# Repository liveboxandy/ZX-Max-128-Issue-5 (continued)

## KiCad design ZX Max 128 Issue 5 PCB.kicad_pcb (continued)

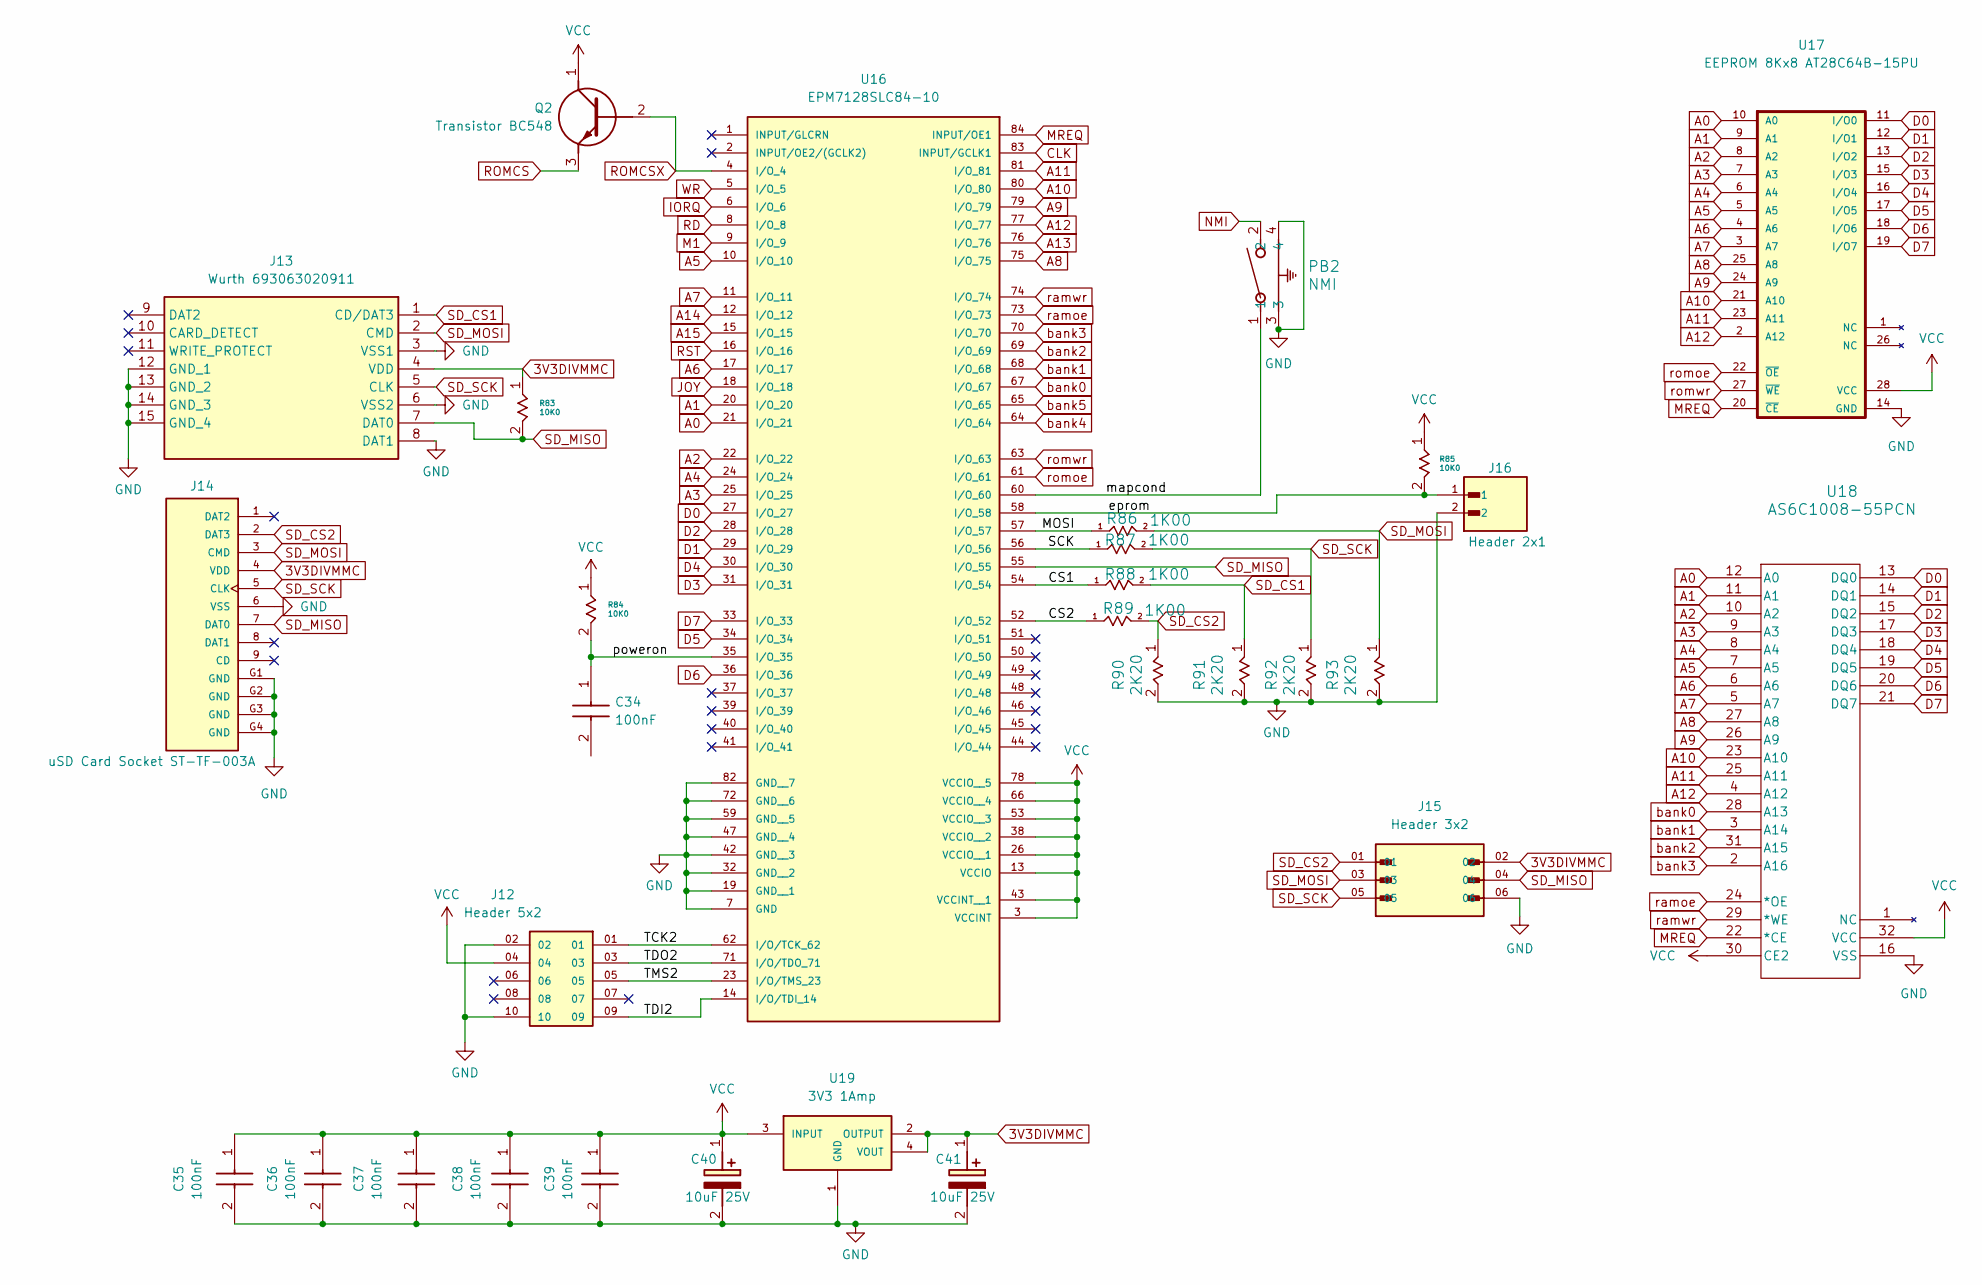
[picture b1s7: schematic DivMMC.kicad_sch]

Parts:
C34, C35, C36, C37, C38, C39: 100nF; CAPRB250W50L400T250H550; Mouser Part Number 594-K104Z15Y5VF5TL2
C40, C41: 10uF 25V; CAPPRD200W50D500H1100; Mouser Part Number 667-ECA-1EM100B
J12: Header 5x2; AMPHENOL_10129381-910002BLF; PARTREV D
J13: Wurth 693063020911; SD Card Connector Wurth 693063020911; Mouser Part Number 710-693063020911
J14: uSD Card Socket ST-TF-003A; SUNTECH_ST-TF-003A
J15: Header 3x2; AMPHENOL_10129381-906002BLF
J16: Header 2x1; HARWIN_M20-9990246; PARTREV 14
PB2: NMI; SW2_1825027-G_TEC
Q2: Transistor BC548; BC548BTA
R83, R84, R85: 10K0; STA_CF14_STP
R86, R87, R88, R89: 1K00; STA_CF14_STP
R90, R91, R92, R93: 2K20; STA_CF14_STP
U16: EPM7128SLC84-10; PLCC84AT
U17: EEPROM 8Kx8 AT28C64B-15PU; DIP1555W45P254L3733H482Q28
U18: AS6C1008-55PCN; PDIP-32_MIL600_ALL
U19: 3V3 1Amp; SOT230P700X185-4N

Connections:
3V3DIVMMC: C41.1 (+), J13.4 (VDD), J14.4 (VDD), J15.02, R83.1, U19.2 (OUTPUT), U19.4 (VOUT)
/DivMMC/CS1: R88.1, U16.54 (I/O_54)
/DivMMC/CS2: R89.1, U16.52 (I/O_52)
/DivMMC/MOSI: R86.1, U16.57 (I/O_57)
/DivMMC/SCK: R87.1, U16.56 (I/O_56)
/DivMMC/TCK2: J12.01, U16.62 (I/O/TCK_62)
/DivMMC/TDI2: J12.09, U16.14 (I/O/TDI_14)
/DivMMC/TDO2: J12.03, U16.71 (I/O/TDO_71)
/DivMMC/TMS2: J12.05, U16.23 (I/O/TMS_23)
/DivMMC/eprom: J16.1, R85.2, U16.58 (I/O_58)
/DivMMC/mapcond: PB2.1, U16.60 (I/O_60)
/DivMMC/poweron: C34.1 (+_1), R84.2, U16.35 (I/O_35)
A0: U16.21 (I/O_21), U17.10 (A0), U18.12 (A0); also elsewhere on the board
A1: U16.20 (I/O_20), U17.9 (A1), U18.11 (A1); also elsewhere on the board
A2: U16.22 (I/O_22), U17.8 (A2), U18.10 (A2); also elsewhere on the board
A3: U16.25 (I/O_25), U17.7 (A3), U18.9 (A3); also elsewhere on the board
A4: U16.24 (I/O_24), U17.6 (A4), U18.8 (A4); also elsewhere on the board
A5: U16.10 (I/O_10), U17.5 (A5), U18.7 (A5); also elsewhere on the board
A6: U16.17 (I/O_17), U17.4 (A6), U18.6 (A6); also elsewhere on the board
A7: U16.11 (I/O_11), U17.3 (A7), U18.5 (A7); also elsewhere on the board
A8: U16.75 (I/O_75), U17.25 (A8), U18.27 (A8); also elsewhere on the board
A9: U16.79 (I/O_79), U17.24 (A9), U18.26 (A9); also elsewhere on the board
A10: U16.80 (I/O_80), U17.21 (A10), U18.23 (A10); also elsewhere on the board
A11: U16.81 (I/O_81), U17.23 (A11), U18.25 (A11); also elsewhere on the board
A12: U16.77 (I/O_77), U17.2 (A12), U18.4 (A12); also elsewhere on the board
A13: U16.76 (I/O_76); also elsewhere on the board
A14: U16.12 (I/O_12); also elsewhere on the board
A15: U16.15 (I/O_15); also elsewhere on the board
CLK: U16.83 (INPUT/GCLK1); also elsewhere on the board
D0: U16.27 (I/O_27), U17.11 (I/O0), U18.13 (DQ0); also elsewhere on the board
D1: U16.29 (I/O_29), U17.12 (I/O1), U18.14 (DQ1); also elsewhere on the board
D2: U16.28 (I/O_28), U17.13 (I/O2), U18.15 (DQ2); also elsewhere on the board
D3: U16.31 (I/O_31), U17.15 (I/O3), U18.17 (DQ3); also elsewhere on the board
D4: U16.30 (I/O_30), U17.16 (I/O4), U18.18 (DQ4); also elsewhere on the board
D5: U16.34 (I/O_34), U17.17 (I/O5), U18.19 (DQ5); also elsewhere on the board
D6: U16.36 (I/O_36), U17.18 (I/O6), U18.20 (DQ6); also elsewhere on the board
D7: U16.33 (I/O_33), U17.19 (I/O7), U18.21 (DQ7); also elsewhere on the board
GND: C35.2 (-), C36.2 (-), C37.2 (-), C38.2 (-), C39.2 (-), C40.2 (-), C41.2 (-), J12.02, J12.10, J13.3 (VSS1), J13.6 (VSS2), J13.8 (DAT1), J13.12 (GND_1), J13.13 (GND_2), J13.14 (GND_3), J13.15 (GND_4), J14.6 (VSS), J14.G1 (GND), J14.G2 (GND), J14.G3 (GND), J14.G4 (GND), J15.06, J16.2, PB2.3, PB2.4, R90.2, R91.2, R92.2, R93.2, U16.7 (GND), U16.19 (GND__1), U16.32 (GND__2), U16.42 (GND__3), U16.47 (GND__4), U16.59 (GND__5), U16.72 (GND__6), U16.82 (GND__7), U17.14 (GND), U18.16 (VSS), U19.1 (GND); also elsewhere on the board
IORQ: U16.6 (I/O_6); also elsewhere on the board
JOY: U16.18 (I/O_18); also elsewhere on the board
M1: U16.9 (I/O_9); also elsewhere on the board
MREQ: U16.84 (INPUT/OE1), U17.20 (~CE), U18.22 (*CE); also elsewhere on the board
NMI: PB2.2; also elsewhere on the board
RD: U16.8 (I/O_8); also elsewhere on the board
ROMCS: Q2.3 (E); also elsewhere on the board
ROMCSX: Q2.2 (B), U16.4 (I/O_4)
RST: U16.16 (I/O_16); also elsewhere on the board
SD_CS1: J13.1 (CD/DAT3), R88.2, R91.1
SD_CS2: J14.2 (DAT3), J15.01, R89.2, R90.1
SD_MISO: J13.7 (DAT0), J14.7 (DAT0), J15.04, R83.2, U16.55 (I/O_55)
SD_MOSI: J13.2 (CMD), J14.3 (CMD), J15.03, R86.2, R93.1
SD_SCK: J13.5 (CLK), J14.5 (CLK), J15.05, R87.2, R92.1
VCC: C35.1 (+), C36.1 (+), C37.1 (+), C38.1 (+), C39.1 (+), C40.1 (+), J12.04, Q2.1 (C), R84.1, R85.1, U16.3 (VCCINT), U16.13 (VCCIO), U16.26 (VCCIO__1), U16.38 (VCCIO__2), U16.43 (VCCINT__1), U16.53 (VCCIO__3), U16.66 (VCCIO__4), U16.78 (VCCIO__5), U17.28 (VCC), U18.30 (CE2), U18.32 (VCC), U19.3 (INPUT); also elsewhere on the board
WR: U16.5 (I/O_5); also elsewhere on the board
bank0: U16.67 (I/O_67), U18.28 (A13)
bank1: U16.68 (I/O_68), U18.3 (A14)
bank2: U16.69 (I/O_69), U18.31 (A15)
bank3: U16.70 (I/O_70), U18.2 (A16)
bank4: U16.64 (I/O_64)
bank5: U16.65 (I/O_65)
ramoe: U16.73 (I/O_73), U18.24 (*OE)
ramwr: U16.74 (I/O_74), U18.29 (*WE)
romoe: U16.61 (I/O_61), U17.22 (~OE)
romwr: U16.63 (I/O_63), U17.27 (~WE)

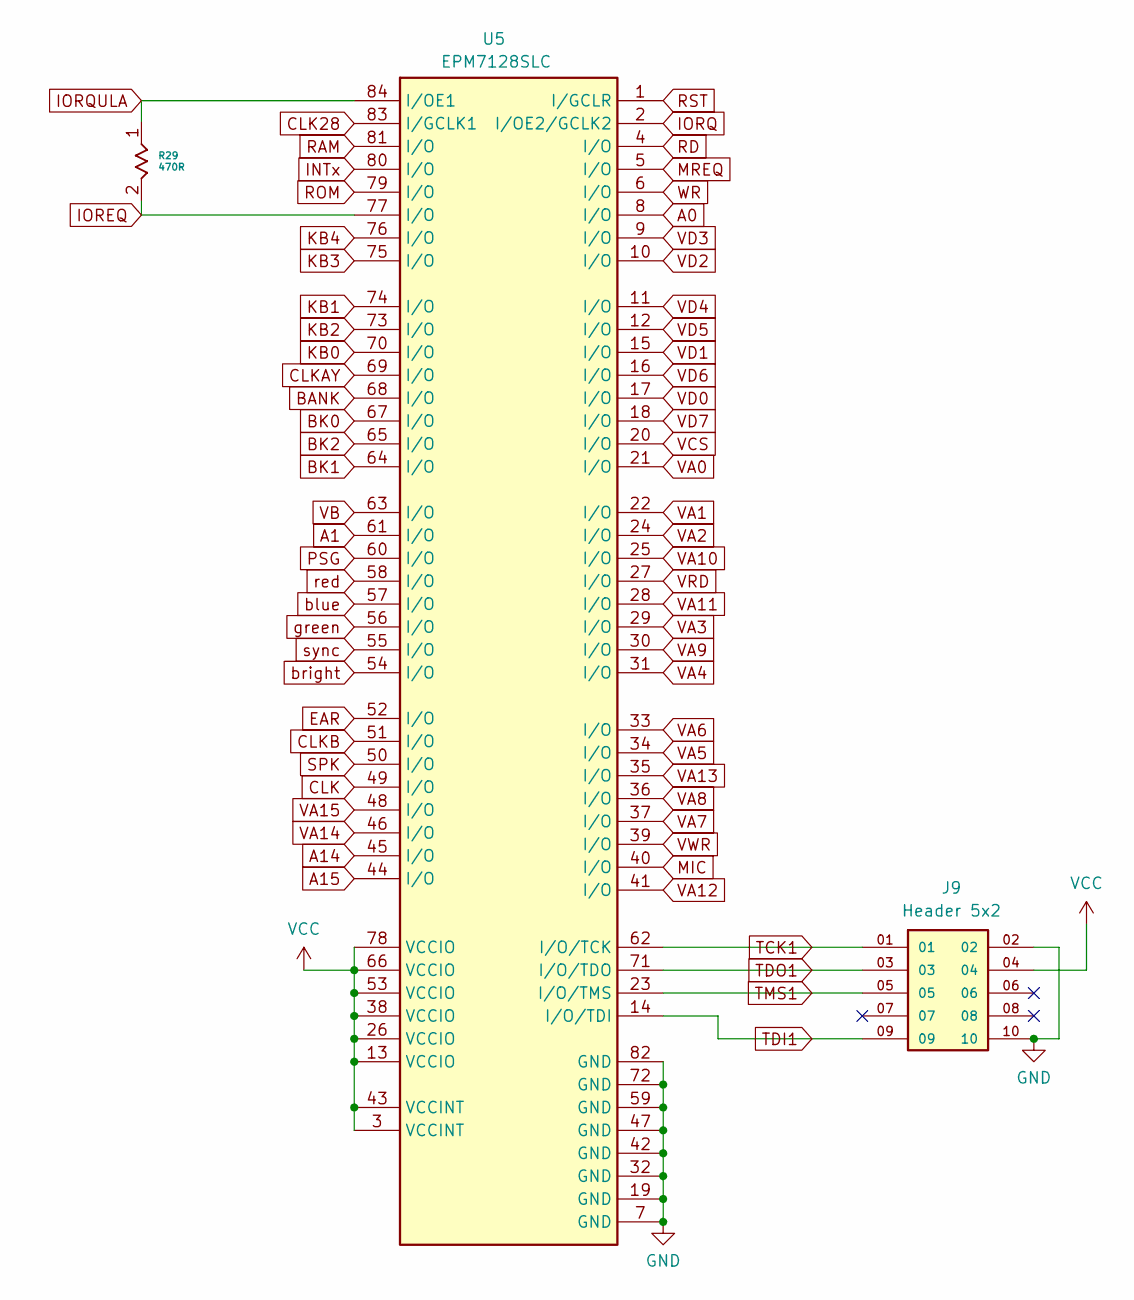
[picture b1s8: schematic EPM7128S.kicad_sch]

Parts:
J9: Header 5x2; AMPHENOL_10129381-910002BLF; PARTREV D
R29: 470R; STA_CF14_STP
U5: EPM7128SLC; PLCC84AT

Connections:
A0: U5.8 (I/O); also elsewhere on the board
A1: U5.61 (I/O); also elsewhere on the board
A14: U5.45 (I/O); also elsewhere on the board
A15: U5.44 (I/O); also elsewhere on the board
BANK: U5.68 (I/O); also elsewhere on the board
BK0: U5.67 (I/O); also elsewhere on the board
BK1: U5.64 (I/O); also elsewhere on the board
BK2: U5.65 (I/O); also elsewhere on the board
CLK: U5.49 (I/O); also elsewhere on the board
CLK28: U5.83 (I/GCLK1); also elsewhere on the board
CLKAY: U5.69 (I/O); also elsewhere on the board
CLKB: U5.51 (I/O); also elsewhere on the board
EAR: U5.52 (I/O); also elsewhere on the board
GND: J9.02, J9.10, U5.7 (GND), U5.19 (GND), U5.32 (GND), U5.42 (GND), U5.47 (GND), U5.59 (GND), U5.72 (GND), U5.82 (GND); also elsewhere on the board
INTx: U5.80 (I/O); also elsewhere on the board
IOREQ: R29.2, U5.77 (I/O)
IORQ: U5.2 (I/OE2/GCLK2); also elsewhere on the board
IORQULA: R29.1, U5.84 (I/OE1); also elsewhere on the board
KB0: U5.70 (I/O); also elsewhere on the board
KB1: U5.74 (I/O); also elsewhere on the board
KB2: U5.73 (I/O); also elsewhere on the board
KB3: U5.75 (I/O); also elsewhere on the board
KB4: U5.76 (I/O); also elsewhere on the board
MIC: U5.40 (I/O); also elsewhere on the board
MREQ: U5.5 (I/O); also elsewhere on the board
PSG: U5.60 (I/O); also elsewhere on the board
RAM: U5.81 (I/O); also elsewhere on the board
RD: U5.4 (I/O); also elsewhere on the board
ROM: U5.79 (I/O); also elsewhere on the board
RST: U5.1 (I/GCLR); also elsewhere on the board
SPK: U5.50 (I/O); also elsewhere on the board
TCK1: J9.01, U5.62 (I/O/TCK)
TDI1: J9.09, U5.14 (I/O/TDI)
TDO1: J9.03, U5.71 (I/O/TDO)
TMS1: J9.05, U5.23 (I/O/TMS)
VA0: U5.21 (I/O); also elsewhere on the board
VA1: U5.22 (I/O); also elsewhere on the board
VA2: U5.24 (I/O); also elsewhere on the board
VA3: U5.29 (I/O); also elsewhere on the board
VA4: U5.31 (I/O); also elsewhere on the board
VA5: U5.34 (I/O); also elsewhere on the board
VA6: U5.33 (I/O); also elsewhere on the board
VA7: U5.37 (I/O); also elsewhere on the board
VA8: U5.36 (I/O); also elsewhere on the board
VA9: U5.30 (I/O); also elsewhere on the board
VA10: U5.25 (I/O); also elsewhere on the board
VA11: U5.28 (I/O); also elsewhere on the board
VA12: U5.41 (I/O); also elsewhere on the board
VA13: U5.35 (I/O); also elsewhere on the board
VA14: U5.46 (I/O); also elsewhere on the board
VA15: U5.48 (I/O); also elsewhere on the board
VB: U5.63 (I/O); also elsewhere on the board
VCC: J9.04, U5.3 (VCCINT), U5.13 (VCCIO), U5.26 (VCCIO), U5.38 (VCCIO), U5.43 (VCCINT), U5.53 (VCCIO), U5.66 (VCCIO), U5.78 (VCCIO); also elsewhere on the board
VCS: U5.20 (I/O); also elsewhere on the board
VD0: U5.17 (I/O); also elsewhere on the board
VD1: U5.15 (I/O); also elsewhere on the board
VD2: U5.10 (I/O); also elsewhere on the board
VD3: U5.9 (I/O); also elsewhere on the board
VD4: U5.11 (I/O); also elsewhere on the board
VD5: U5.12 (I/O); also elsewhere on the board
VD6: U5.16 (I/O); also elsewhere on the board
VD7: U5.18 (I/O); also elsewhere on the board
VRD: U5.27 (I/O); also elsewhere on the board
VWR: U5.39 (I/O); also elsewhere on the board
WR: U5.6 (I/O); also elsewhere on the board
blue: U5.57 (I/O); also elsewhere on the board
bright: U5.54 (I/O); also elsewhere on the board
green: U5.56 (I/O); also elsewhere on the board
red: U5.58 (I/O); also elsewhere on the board
sync: U5.55 (I/O); also elsewhere on the board

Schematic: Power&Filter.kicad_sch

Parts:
C4: 10uF 25V; CAPPRD200W50D500H1100; Mouser Part Number 667-ECA-1EM100B
C5: 22uF 16V; CAPPRD200W50D500H1100; Mouser Part Number 667-ECA-1EM100B
C8: 220uF 16V; CAPPRD200W50D500H1100
C9, C10, C11, C12, C13, C14, C15, C16, C17, C19, C20: 100nF; CAPRB250W50L400T250H550; Mouser Part Number 594-K104Z15Y5VF5TL2
D28: DF02M; DIP825W58P510L832H543Q4N; Mouser Part Number 621-DF02M
J3: ZX_48K_EDGE; ZX_BUS_B_TOP
J4: PJ-002A; CUI_PJ-002A
J17: Header 2x1; HARWIN_M20-9990246; PARTREV 14
U14: R-78E5.0-1.0; CONV_R-78E5.0-1.0; PARTREV 6

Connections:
+9V: C4.1 (+), D28.1 (+), J3.A4 (+9), U14.1 (+VIN)
+12V: J3.B22 (+12)
-5V: J3.B20 (-5)
-12V: J3.B23 (-12)
A0: J3.A9 (A0); also elsewhere on the board
A1: J3.A10 (A1); also elsewhere on the board
A2: J3.A11 (A2); also elsewhere on the board
A3: J3.A12 (A3); also elsewhere on the board
A4: J3.A24 (A4); also elsewhere on the board
A5: J3.A23 (A5); also elsewhere on the board
A6: J3.A22 (A6); also elsewhere on the board
A7: J3.A21 (A7); also elsewhere on the board
A8: J3.B26 (A8); also elsewhere on the board
A9: J3.A27 (A9); also elsewhere on the board
A10: J3.B27 (A10); also elsewhere on the board
A11: J3.A28 (A11); also elsewhere on the board
A12: J3.A2 (A12); also elsewhere on the board
A13: J3.B2 (A13); also elsewhere on the board
A14: J3.A1 (A14); also elsewhere on the board
A15: J3.B1 (A15); also elsewhere on the board
BUSAK: J3.A26 (BUSACK); also elsewhere on the board
BUSRQ: J3.A19 (BUSRQ); also elsewhere on the board
CLKB: J3.A8 (CLOCK); also elsewhere on the board
D0: J3.B6 (D0); also elsewhere on the board
D1: J3.B7 (D1); also elsewhere on the board
D2: J3.B8 (D2); also elsewhere on the board
D3: J3.B11 (D3); also elsewhere on the board
D4: J3.B12 (D4); also elsewhere on the board
D5: J3.B10 (D5); also elsewhere on the board
D6: J3.B9 (D6); also elsewhere on the board
D7: J3.B3 (D7); also elsewhere on the board
GND: C4.2 (-), C5.2 (-), C8.2, C9.2 (-), C10.2 (-), C11.2 (-), C12.2 (-), C13.2 (-), C14.2 (-), C15.2 (-), C16.2 (-), C17.2 (-), C19.2 (-), C20.2 (-), D28.2 (-), J3.A6 (GND), J3.A7 (GND), J3.A14 (GND), J17.2, U14.2 (GND); also elsewhere on the board
HALT: J3.B15 (HALT); also elsewhere on the board
INT: J3.B13 (INT); also elsewhere on the board
IORQ: J3.B17 (IOREQ); also elsewhere on the board
IORQULA: J3.A13 (IORQGE); also elsewhere on the board
M1: J3.B24 (M1); also elsewhere on the board
MREQ: J3.B16 (MREQ); also elsewhere on the board
NMI: J3.B14 (NMI); also elsewhere on the board
unnamed: D28.3 (~_1), J4.1
unnamed: D28.4 (~_2), J4.2, J4.3
RD: J3.B18 (RD); also elsewhere on the board
RFSH: J3.B25 (RFSH); also elsewhere on the board
ROMCS: J3.A25 (ROMCS); also elsewhere on the board
RST: J3.A20 (RESET); also elsewhere on the board
VCC: C5.1 (+), C8.1, C9.1 (+), C10.1 (+), C11.1 (+), C12.1 (+), C13.1 (+), C14.1 (+), C15.1 (+), C16.1 (+), C17.1 (+), C19.1 (+), C20.1 (+), J3.A3 (+5), J17.1, U14.3 (+VOUT); also elsewhere on the board
WAIT: J3.B21 (WAIT); also elsewhere on the board
WR: J3.B19 (WR); also elsewhere on the board

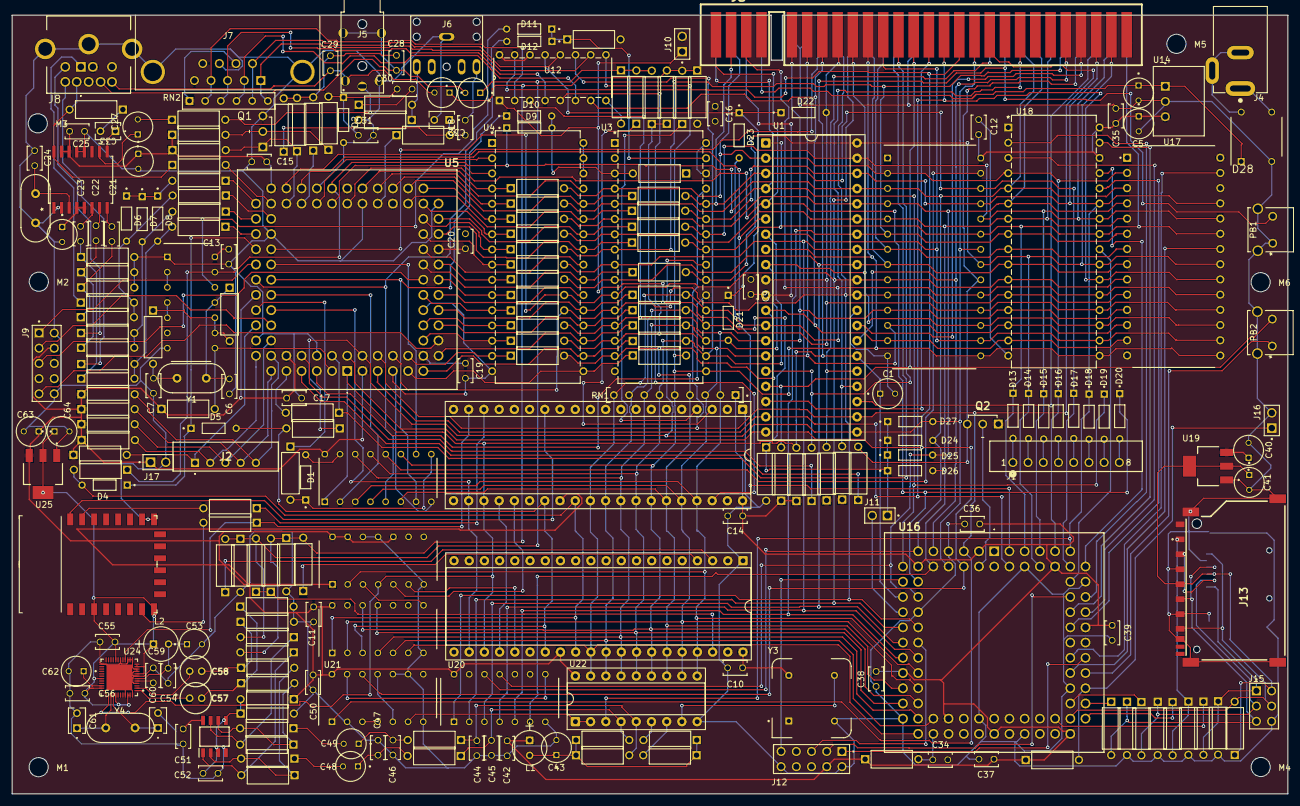
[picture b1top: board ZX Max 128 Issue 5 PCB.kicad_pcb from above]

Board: 2 copper layers, 213.0 x 130.0 mm, 262 parts (1 on the bottom side), 231 nets.

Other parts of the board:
C2, C3: 10uF 25V; CAPPRD200W50D500H1100
D4, D5: 1N4148; DIOAD753W49L380D172B
J5: AV Jack; PJ-322A
R57, R58, R81, R82: 470R; STA_CF14_STP
R59, R62, R63, R64, R65, R68, R69, R70: 1K00; STA_CF14_STP
R60, R61, R66, R67: 2K20; STA_CF14_STP
U8, U9: AY-3-8910; Z80_Socket
U10: CD74HC30E; DIP794W53P254L1930H508Q14N
U11: 74HC74; DIP794W53P254L1930H508Q14N
U15: ESP8266-12E; WIFI_Module_ESP8266_12E

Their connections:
+3V3D: U15.3 (EN), U15.8 (VCC); also elsewhere on the board
A14: R57.1; also elsewhere on the board
A-AY: R59.1, U8.4 (CHANNEL_A)
A-AY2: R65.1, U9.4 (CHANNEL_A)
AY1: U8.25 (A8), U11.5 (Q)
AY2: U9.25 (A8), U11.6 (~Q)
Audio-L: C3.2 (-), J5.3; also elsewhere on the board
Audio-R: C2.2 (-), J5.4; also elsewhere on the board
B-AY: R62.1, U8.3 (CHANNEL_B)
B-AY2: R68.1, U9.3 (CHANNEL_B)
BC1: D4.A, R57.2, U8.29 (BC1), U9.29 (BC1), U10.1
BDIR: D5.A, R58.2, U8.27 (BDIR), U9.27 (BDIR), U10.3
C-AY: R60.1, R61.1, U8.38 (CHANNEL_C)
CLKAY: U8.22 (CLK), U9.22 (CLK); also elsewhere on the board
Comp: J5.1; also elsewhere on the board
D0: U8.37 (DA0), U9.37 (DA0), U11.2 (D); also elsewhere on the board
D1: U8.36 (DA1), U9.36 (DA1), U10.2; also elsewhere on the board
D2: U8.35 (DA2), U9.35 (DA2); also elsewhere on the board
D3: U8.34 (DA3), U9.34 (DA3), U10.12; also elsewhere on the board
D4: U8.33 (DA4), U9.33 (DA4), U10.11; also elsewhere on the board
D5: U8.32 (DA5), U9.32 (DA5), U10.4; also elsewhere on the board
D6: U8.31 (DA6), U9.31 (DA6), U10.5; also elsewhere on the board
D7: U8.30 (DA7), U9.30 (DA7), U10.6; also elsewhere on the board
GND: J5.2, R63.2, R64.2, R69.2, R70.2, U8.1 (VSS), U8.24 (~A9), U9.1 (VSS), U9.24 (~A9), U10.7 (GND), U11.7 (GND), U11.11 (C), U11.12 (D), U15.15 (GND), U15.16 (TXD2/IO15); also elsewhere on the board
IN4: U8.14 (IOA7), U15.22 (TXD0/TXD)
L-in: C3.1 (+), R61.2, R62.2, R64.1, R67.2, R68.2, R70.1; also elsewhere on the board
MIDI: R81.2, U15.7 (MOSI/IO13)
unnamed: R66.1, R67.1, U9.38 (CHANNEL_C)
unnamed: U10.8, U11.3 (C)
unnamed: R82.2, U15.21 (RXD0/RXD)
OUT3: R81.1, U8.19 (IOA2); also elsewhere on the board
OUT4: R82.1, U8.18 (IOA3)
PSG: D4.K, D5.K; also elsewhere on the board
R-in: C2.1 (+), R59.2, R60.2, R63.1, R65.2, R66.2, R69.1; also elsewhere on the board
RD: R58.1; also elsewhere on the board
RST: U8.23 (~RESET), U9.23 (~RESET), U11.4 (~S); also elsewhere on the board
VCC: U8.28 (BC2), U8.40 (VCC), U9.28 (BC2), U9.40 (VCC), U10.14 (VCC), U11.1 (~R), U11.10 (~S), U11.13 (~R), U11.14 (VCC); also elsewhere on the board

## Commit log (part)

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2026-02-06 Enhance README with warnings and usage notes
    Added warnings and clarifications about the PCB layout and usage.
